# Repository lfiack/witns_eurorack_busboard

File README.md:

# witns_eurorack_busboard
Eurorack bus board

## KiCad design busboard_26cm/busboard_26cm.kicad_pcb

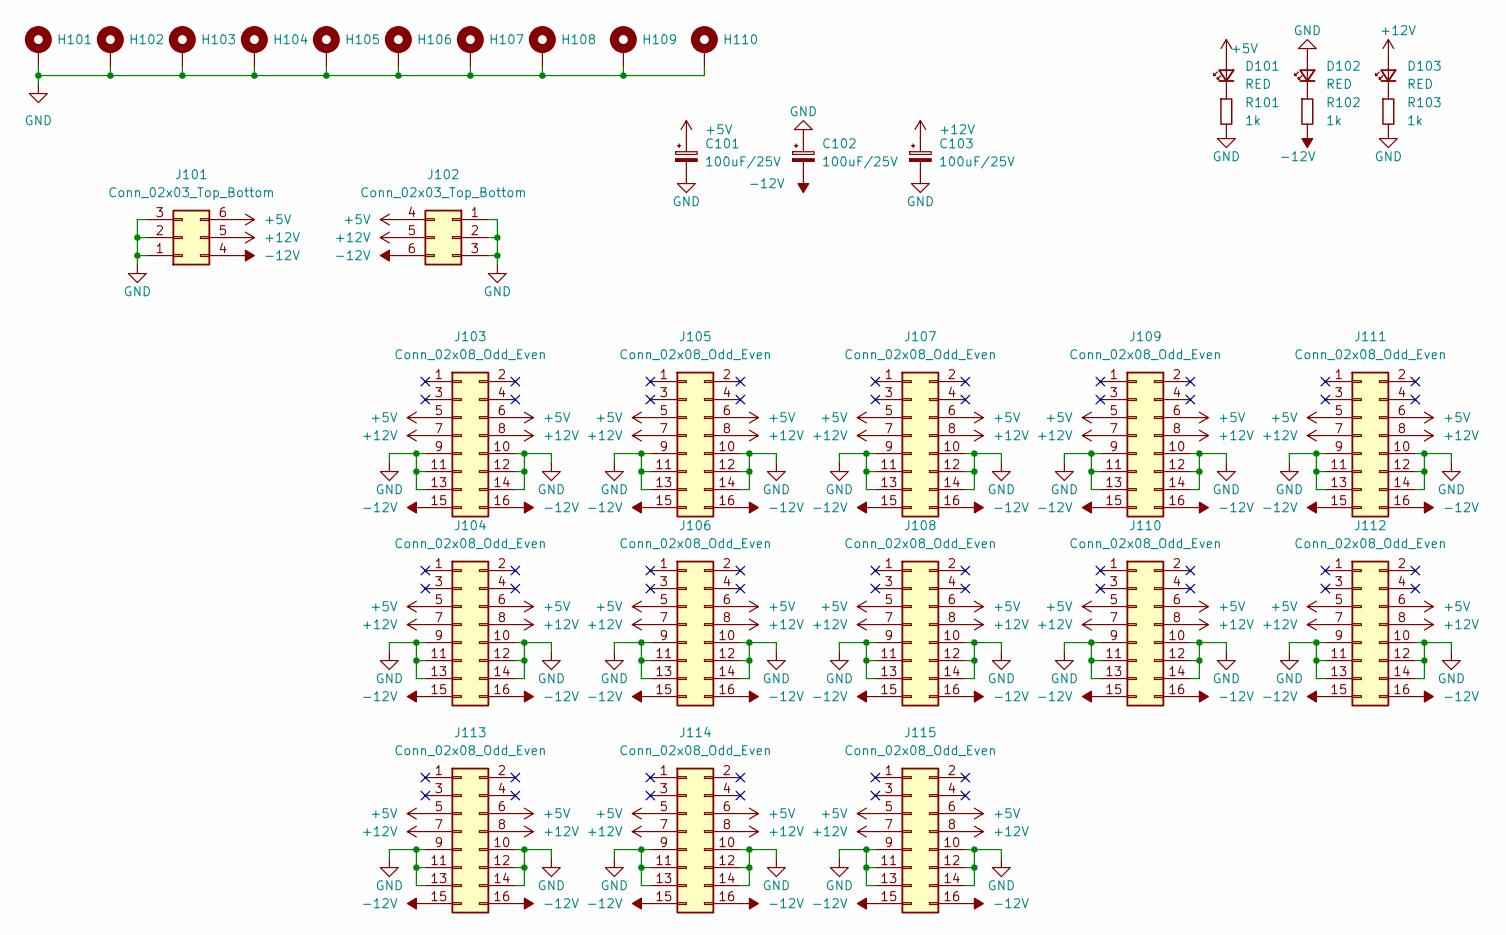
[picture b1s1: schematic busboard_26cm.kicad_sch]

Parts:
C101, C102, C103: 100uF/25V; CP_Elec_6.3x7.7
D101, D102, D103: RED; LED_0603_1608Metric
H101, H102, H103, H104, H105, H106, H107, H108, H109, H110: MountingHole_Pad; MountingHole_3.2mm_M3_Pad_Via
J101, J102: Conn_02x03_Top_Bottom; Molex_Mini-Fit_Jr_5569-06A2_2x03_P4.20mm_Horizontal
J103, J104, J105, J106, J107, J108, J109, J110, J111, J112, J113, J114, J115: Conn_02x08_Odd_Even; IDC-Header_2x08_P2.54mm_Vertical
R101, R102, R103: 1k; R_0603_1608Metric

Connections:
+5V: C101.1, D101.2 (A), J101.6, J102.4, J103.5, J103.6, J104.5, J104.6, J105.5, J105.6, J106.5, J106.6, J107.5, J107.6, J108.5, J108.6, J109.5, J109.6, J110.5, J110.6, J111.5, J111.6, J112.5, J112.6, J113.5, J113.6, J114.5, J114.6, J115.5, J115.6
+12V: C103.1, D103.2 (A), J101.5, J102.5, J103.7, J103.8, J104.7, J104.8, J105.7, J105.8, J106.7, J106.8, J107.7, J107.8, J108.7, J108.8, J109.7, J109.8, J110.7, J110.8, J111.7, J111.8, J112.7, J112.8, J113.7, J113.8, J114.7, J114.8, J115.7, J115.8
-12V: C102.2, J101.4, J102.6, J103.15, J103.16, J104.15, J104.16, J105.15, J105.16, J106.15, J106.16, J107.15, J107.16, J108.15, J108.16, J109.15, J109.16, J110.15, J110.16, J111.15, J111.16, J112.15, J112.16, J113.15, J113.16, J114.15, J114.16, J115.15, J115.16, R102.2
GND: C101.2, C102.1, C103.2, D102.2 (A), H101.1, H102.1, H103.1, H104.1, H105.1, H106.1, H107.1, H108.1, H109.1, H110.1, J101.1, J101.2, J101.3, J102.1, J102.2, J102.3, J103.9, J103.10, J103.11, J103.12, J103.13, J103.14, J104.9, J104.10, J104.11, J104.12, J104.13, J104.14, J105.9, J105.10, J105.11, J105.12, J105.13, J105.14, J106.9, J106.10, J106.11, J106.12, J106.13, J106.14, J107.9, J107.10, J107.11, J107.12, J107.13, J107.14, J108.9, J108.10, J108.11, J108.12, J108.13, J108.14, J109.9, J109.10, J109.11, J109.12, J109.13, J109.14, J110.9, J110.10, J110.11, J110.12, J110.13, J110.14, J111.9, J111.10, J111.11, J111.12, J111.13, J111.14, J112.9, J112.10, J112.11, J112.12, J112.13, J112.14, J113.9, J113.10, J113.11, J113.12, J113.13, J113.14, J114.9, J114.10, J114.11, J114.12, J114.13, J114.14, J115.9, J115.10, J115.11, J115.12, J115.13, J115.14, R101.2, R103.2
unnamed: D101.1 (K), R101.1
unnamed: D102.1 (K), R102.1
unnamed: D103.1 (K), R103.1

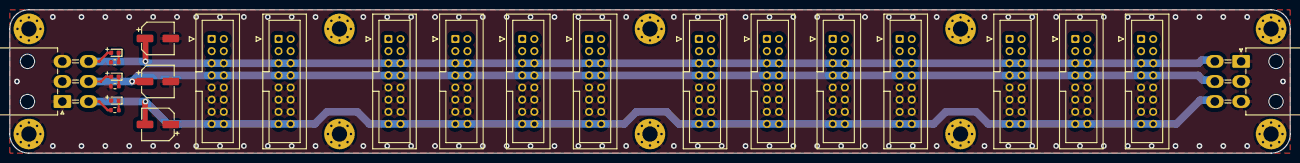
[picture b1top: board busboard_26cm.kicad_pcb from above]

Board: 2 copper layers, 268.0 x 30.0 mm, 34 parts (0 on the bottom side), 7 nets.

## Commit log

2023-03-30 placement
2023-03-30 other connectors
2023-03-31 20cm busboard PCB
2023-06-09 busboard 26cm
